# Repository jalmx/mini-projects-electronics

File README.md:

# Colección de Proyectos Electronicos

Este repositorio contiene una colección de diversos proyectos pequeños de diseño de PCB realizados en KiCad. Cada subdirectorio representa un proyecto independiente con sus propios esquemáticos y archivos de diseño.

## 📂 Contenido del Repositorio

Actualmente, el repositorio incluye los siguientes proyectos:

*   **board_7seg**: Proyecto base de visualización de 7 segmentos.
*   
*   **big-display**: Display de 7 segmentos de grande.

## 🚀 Requisitos

*   **KiCad**: Se recomienda utilizar la versión 8.0 o superior para asegurar compatibilidad con todos los archivos.

## 🛠️ Estructura de los Proyectos

Cada carpeta de proyecto suele contener:
*   `*.kicad_pro`: Archivo principal del proyecto.
*   `*.kicad_sch`: Archivos del esquemático electrónico.
*   `*.kicad_pcb`: Archivo del diseño de la placa (layout).

## 📄 Licencia

Este proyecto se distribuye bajo la licencia **CERN Open Hardware Licence Version 2 - Weakly Reciprocal (CERN-OHL-W-2.0)**.
Consulta el archivo [LICENSE](LICENSE) para más detalles.

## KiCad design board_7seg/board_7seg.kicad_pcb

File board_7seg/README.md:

# Board 7-Segment Display

Este proyecto consiste en una placa de circuito impreso (PCB) diseñada en KiCad para controlar y visualizar información utilizando displays de 7 segmentos.

## 📋 Descripción

El objetivo de este diseño es proporcionar una interfaz visual simple mediante displays de 7 segmentos.
*(Aquí puedes añadir más detalles: ¿Es para un microcontrolador específico? ¿Qué tamaño de displays usa? ¿Es ánodo o cátodo común?)*

## ⚙️ Características Técnicas

*   **Software de Diseño**: KiCad 8.0 (o compatible)
*   **Capas**: 2 capas (Top/Bottom) *[Ajustar si es diferente]*
*   **Dimensiones**: *[Añadir dimensiones si se conocen]*

## 📁 Archivos del Proyecto

*   `board_7seg.kicad_sch`: Esquemático del circuito.
*   `board_7seg.kicad_pcb`: Diseño del PCB (Layout).
*   `board_7seg.kicad_pro`: Archivo de proyecto principal.

## 🔧 Montaje y BOM

La lista de materiales (BOM) se puede generar desde el esquemático. Los componentes principales incluyen:
*   Displays de 7 segmentos.
*   Resistencias limitadoras de corriente.
*   Conectores (Headers).

## 🚀 Uso

1.  Abrir `board_7seg.kicad_pro` con KiCad.
2.  Revisar el esquemático para entender las conexiones.
3.  Generar los archivos Gerber desde el editor de PCB para la fabricación.

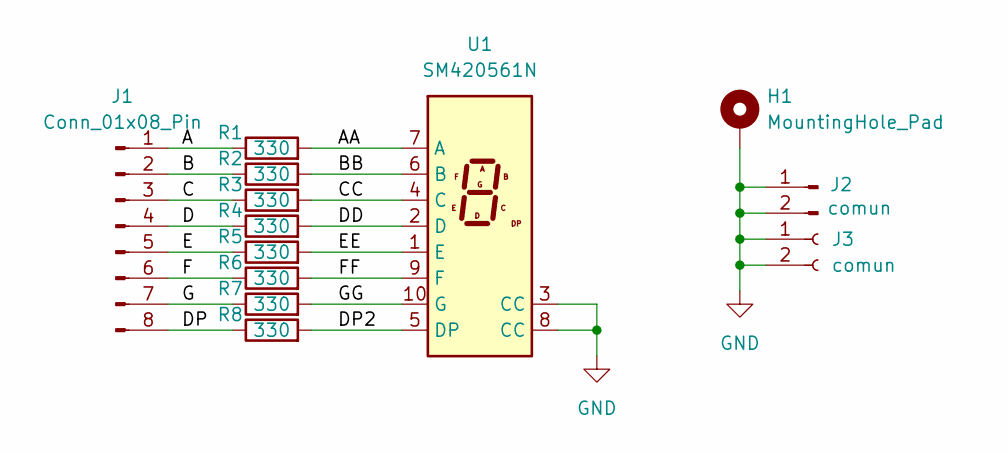
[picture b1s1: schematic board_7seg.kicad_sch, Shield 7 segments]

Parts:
H1: MountingHole_Pad; MountingHole_2.2mm_M2_Pad
J1: Conn_01x08_Pin; PinHeader_1x08_P2.54mm_Vertical
J2: comun; PinHeader_1x02_P2.54mm_Vertical
J3: comun; PinSocket_1x02_P2.54mm_Vertical
R1, R2, R3, R4, R5, R6, R7, R8: 330; R_Axial_DIN0309_L9.0mm_D3.2mm_P12.70mm_Horizontal
U1: SM420561N; 7SegmentLED_LTS6760_LTS6780

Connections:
/A: J1.1, R1.1
/AA: R1.2, U1.7 (A)
/B: J1.2, R2.1
/BB: R2.2, U1.6 (B)
/C: J1.3, R3.1
/CC: R3.2, U1.4 (C)
/D: J1.4, R4.1
/DD: R4.2, U1.2 (D)
/DP: J1.8, R8.1
/DP2: R8.2, U1.5 (DP)
/E: J1.5, R5.1
/EE: R5.2, U1.1 (E)
/F: J1.6, R6.1
/FF: R6.2, U1.9 (F)
/G: J1.7, R7.1
/GG: R7.2, U1.10 (G)
GND: H1.1, J2.1, J2.2, J3.1, J3.2, U1.3 (CC), U1.8 (CC)

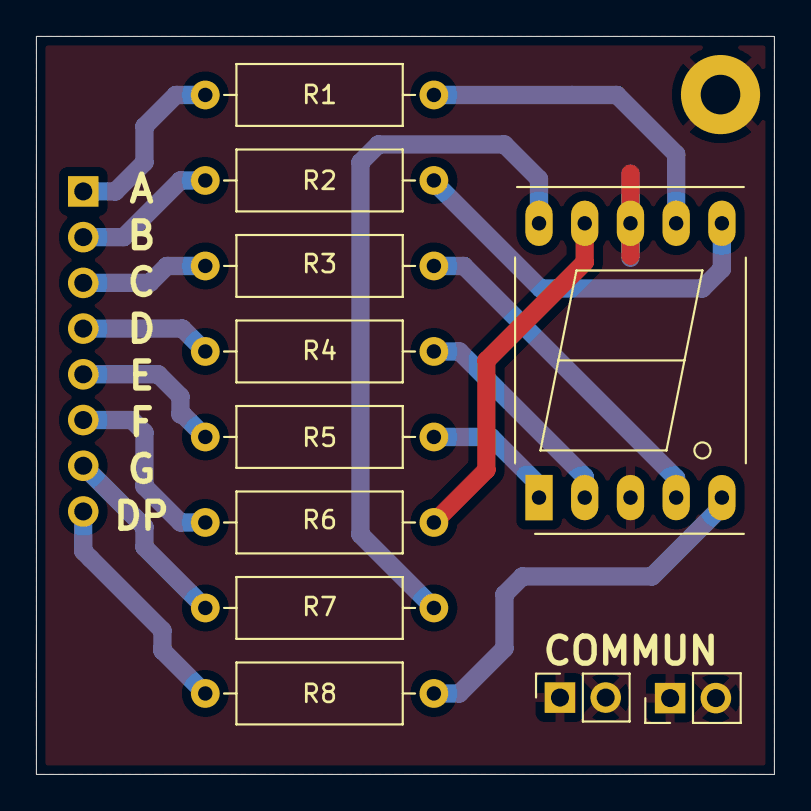
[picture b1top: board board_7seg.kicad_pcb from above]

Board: 2 copper layers, 41.0 x 41.0 mm, 13 parts (1 on the bottom side), 17 nets.

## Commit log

2025-12-21 add: init
2026-06-14 add: imgs in board_7_seg
